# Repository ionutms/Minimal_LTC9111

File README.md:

# Minimal_LTC9111

## Overview

This repository contains a minimal KiCad design project for the Analog Devices LTC9111, an industrial Single-Pair Power over Ethernet (SPoE) Powered Device (PD) controller. The project is compliant with the IEEE 802.3cg standard and is designed for use in building and factory automation, security systems, and traffic control systems.

## Disclaimer

> [!NOTE]
> This project is provided "as is" and without any warranty, express or implied. For more details, please see the [LICENSE](LICENSE) file.

## About the LTC9111

The LTC9111 from Analog Devices is an industrial Single-Pair Power over Ethernet (SPoE) Powered Device (PD) controller. It is compliant with the IEEE 802.3cg standard and is designed for use in building and factory automation, security systems, and traffic control systems.

Key features include:

- **Wide Input Voltage Range:** The device operates with an input voltage from 2.3V to 60V.
- **Serial Communication Classification Protocol (SCCP):** This ensures that full operating voltage is only applied by the Power Sourcing Equipment (PSE) when a valid PD is connected.
- **Polarity Correction:** It drives low-side bridge MOSFETs for polarity correction.
- **Integrated Standby Regulator:** The LTC9111 includes an integrated 3.5V standby regulator.
- **Low Current Consumption:** It has a maximum current of 150µA during classification.
- **External MOSFET Drive:** It drives external N-channel MOSFETs for classification and to isolate output capacitance.
- **Package Options:** The LTC9111 is available in 12-pin MSOP and DFN 4mm × 3mm packages.
- **Temperature Range:** It has an operating junction temperature range of -40°C to +150°C.

## Project Structure

```
minimal_ltc9111/
├── minimal_ltc9111.kicad_sch       # Main schematic file
├── minimal_ltc9111.kicad_pcb       # PCB layout file
├── minimal_ltc9111.kicad_pro       # Project configuration file
├── fp-lib-table                     # Footprint library table
├── sym-lib-table                    # Symbol library table
├── project_jobs_set.kicad_jobset    # Project job settings
├── ibom.config.ini                  # Interactive BOM configuration
├── docs/                            # Documentation files
│   ├── pictures/                    # Images and photos
│   ├── schematics/                  # Schematic PDF exports
│   └── 3d_models/                   # 3D model files
└── KiCAD_Symbols_Generator/         # Submodule for symbol generation from CSV data
```

## Project Features

This design provides a minimal implementation of the LTC9111 with the following features:

- **Power Supply:**
  - VIN: +3.3V
- **Channel Configuration:**
  - Basic protection circuits for the Ethernet twisted pair.
- **Bill of Materials (BOM):**
  - Interactive HTML BOM (`ibom.html`) for easy component identification and sourcing.
- **Libraries:**
  - Comprehensive symbol and footprint libraries integrated as a submodule.
- **3D Model:**
  - Includes a 3D model of the board for better visualization.

## Getting Started

### Prerequisites

- [KiCad EDA](https://www.kicad.org/) version 9.0 or later installed on your system
- Git (for cloning the repository and submodule management)

### Opening the Project

1. **Clone the repository** (including submodules):
   ```bash
   git clone --recursive https://github.com/ionutms/Minimal_LTC9111.git
   ```
   
   If you've already cloned the repository without submodules, initialize them with:
   ```bash
   git submodule init
   git submodule update
   ```

2. **Open the project in KiCad**:
   - Launch KiCad
   - Click "Open Existing Project"
   - Navigate to the cloned repository folder
   - Select the `minimal_ltc9111.kicad_pro` file

3. **Explore the design**:
   - Open the schematic editor to view the circuit design
   - Open the PCB editor to view the board layout
   - Review the symbol and footprint libraries used in the design

### Project Files

- **Main schematic**: `minimal_ltc9111.kicad_sch` - Contains the primary circuit design with the LTC9111 and support components
- **PCB layout**: `minimal_ltc9111.kicad_pcb` - Physical board design file with proper component placement
- **Project configuration**: `minimal_ltc9111.kicad_pro` - KiCad project settings

## Dependencies

This project has the following dependencies:

### 1. KiCAD Symbols Generator

This repository uses [KiCAD_Symbols_Generator](https://github.com/ionutms/KiCAD_Symbols_Generator) as a submodule for custom symbol generation.

To initialize the submodule after cloning this repository:

```bash
git submodule update --init --recursive
```

### 2. 3D Models

This project requires the [3D_Models_Vault](https://github.com/ionutms/3D_Models_Vault) repository for 3D models.

#### Setup for KiCAD 9:

1. Clone the 3D models repository:
   ```bash
   git clone https://github.com/ionutms/3D_Models_Vault.git
   ```

2. In KiCAD 9, add an environment variable:
   - Variable name: `KICAD9_3D_MODELS_VAULT`
   - Variable value: Full path to where you cloned the 3D_Models_Vault repository

## Usage

After setting up the dependencies, open the project in KiCAD 9 to access all features including the 3D models.

## Symbol Generator Submodule

This project includes the KiCAD_Symbols_Generator as a submodule, which provides tools for generating KiCad symbols from CSV data files. For more information on using this tool, see the [KiCAD_Symbols_Generator documentation](minimal_ltc9111/KiCAD_Symbols_Generator/README.md).

## Documentation

The `docs` folder contains:
- Schematic PDF exports
- Images and photos of the design
- 3D model files (GLB and WRL formats)

## Visuals

The following images showcase the PCB design from different perspectives:

*Top View of the PCB*

*Side View of the PCB*

*Bottom View of the PCB*

## License

This project is licensed under the MIT License - see the [LICENSE](LICENSE) file for details.

## References

- [LTC9111 Datasheet](https://www.analog.com/media/en/technical-documentation/data-sheets/LTC9111.pdf)
- [KiCad EDA](https://www.kicad.org/)

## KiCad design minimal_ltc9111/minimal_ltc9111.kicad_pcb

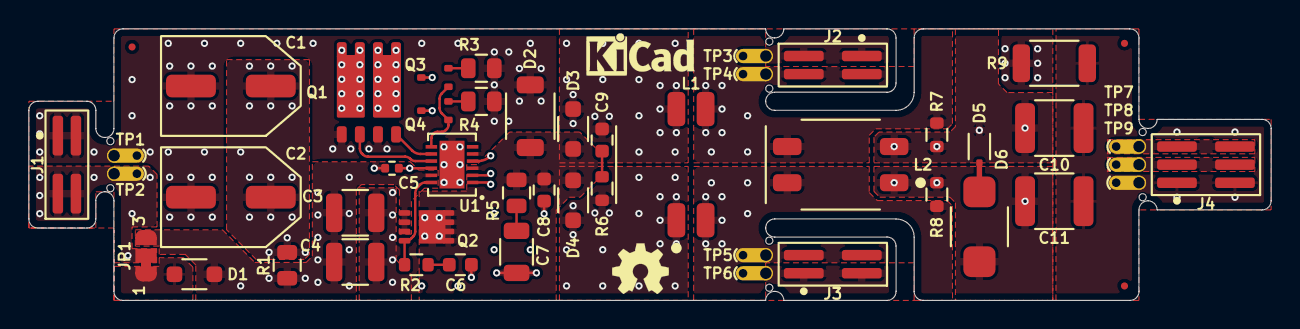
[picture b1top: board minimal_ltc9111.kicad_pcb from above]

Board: 4 copper layers, 87.1 x 19.0 mm, 54 parts (0 on the bottom side), 24 nets.

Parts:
C1, C2: 22 µF; C_023x0248_5_9x6_3Metric
C3, C4: 4.7 µF; C_1210_200_3225Metric
C5: 2.2 µF; C_0402_1005Metric
C6: 22 nF; C_0603_1608Metric
C7: 150 nF; C_1206_3216Metric
C8, C9: 47 nF; C_0603_1608Metric
C10, C11: 100 pF; C_1812_4532Metric
D1, D3, D4: 100.0 V; SOD123W
D2: 58 V; SOD128
D5: 3.3 V; SOD323
D6: 58 V; DO-214AA
FID1, FID2, FID3: Fiducial; Fiducial_0.5mm_Mask1mm
J1, J2, J3: FW-02-03-G-D-085-155
J4: FW-03-03-G-D-085-155
JP1: SolderJumper_3_Open; SolderJumper-3_P1.3mm_Bridged_1_2_RoundedPad1.0x1.5mm_Numbe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
L1: 68.0 µH; MSD1048
L2: 470 µH; SRF0905A
MB1, MB2, MB3: mouse-bite-midle-50mil-200mil
MB6: mouse-bite-50mil-200mil; mouse-bite-50mil-250mil
Q1: 100 V; LFPAK56D-8
Q2: 100.0 V; LFPAK33-8
Q3, Q4: 100 V; SOT-323
R1, R3, R4: 3.3 Ω; R_0805_2012Metric
R2, R6: 100 Ω; R_0603_1608Metric
R5: 40.2 Ω; R_0805_2012Metric
R7, R8: 10 kΩ; R_0603_1608Metric
R9: 4.7 MΩ; R_2010_5025Metric
TP1, TP2, TP3, TP4, TP5, TP6, TP7, TP8, TP9: TestPoint; TestPoint_THTPad_Castelated
U1: LTC9111RDE-PBF; 05-08-1695_ADI

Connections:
/BULK_OUT: C1.1, C2.1, R1.2
/CABLE+: C10.1, D5.1, J4.5, J4.6, L2.2, R7.1, TP7.1
/CABLE-: C11.1, D6.2, J4.3, J4.4, L2.1, R8.1, TP8.1
/IN: C8.1, D2.1, D3.1, D4.1, Q2.5 (D), R5.1, U1.3 (IN)
/LGATE1: Q1.2 (G1), U1.9 (LGATE1)
/LGATE2: Q1.4 (G2), U1.8 (LGATE2)
/OUT: C3.1, C4.1, D1.2, JP1.3 (B), Q2.1 (S), Q2.2 (S), Q2.3 (S), R1.1, U1.11 (OUT)
/OUT_SELECTED: J1.2, J1.4, JP1.2 (C), TP2.1
/POWER_IN_N: J3.3, J3.4, L1.2, L2.4, R8.2, TP5.1
/POWER_IN_P: J2.3, J2.4, L1.3, L2.3, R7.2, TP4.1
/POWER_N: C9.2, D3.2, L1.4, Q1.5 (D2), Q3.3 (D), U1.2 (SNS2)
/POWER_P: D4.2, L1.1, Q1.6 (D1), Q4.3 (D), R6.1, U1.1 (SNS1)
/SCCP: Q3.1 (G), Q4.1 (G), U1.7 (SCCP)
/STBY: C5.1, U1.4 (STBY), U1.10 (CLASSC)
Earth: C10.2, C11.2, J4.1, J4.2, R9.1, TP9.1
GND: C1.2, C2.2, C3.2, C4.2, C5.2, C6.2, C7.2, C8.2, D2.2, J1.1, J1.3, J2.1, J2.2, J3.1, J3.2, Q1.1 (S1), Q1.3 (S2), R3.2, R4.2, R9.2, TP1.1, TP3.1, TP6.1, U1.5 (CLASSV), U1.13 (GND)
unnamed: C6.1, R2.2
unnamed: C7.1, R5.2
unnamed: C9.1, R6.2
unnamed: D5.2, D6.1
unnamed: D1.1, JP1.1 (A)
unnamed: Q2.4 (G), R2.1, U1.12 (GATE)
unnamed: Q3.2 (S), R3.1
unnamed: Q4.2 (S), R4.1

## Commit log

2025-02-07 Add initial KiCad project files for minimal_ltc9111
2025-02-07 Add KiCad Symbol Generator submodule and library tables for minimal_ltc9111
2025-02-10 Add initial project files
2025-02-10 Backup
2025-02-10 Add glb 3D model
2025-02-24 Update UUIDs and add 3D viewer link in PCB and schematic files
2025-02-27 Update subproject commit in KiCAD_Symbol_Generator
2025-02-27 Update subproject commit and enhance component blacklist in ibom.config.ini; add new libraries in fp-lib-table and sym-lib-table
2025-02-27 Update minimal_ltc9111.glb binary file
2025-03-10 Update subproject commit in KiCAD_Symbol_Generator and modify minimal_ltc9111.glb binary file
2025-03-16 Remove submodule reference for KiCAD_Symbol_Generator
2025-03-16 Add submodule reference for KiCAD_Symbols_Generator
2025-03-16 Update footprint library URIs to reference KiCAD_Symbols_Generator
2025-03-18 Switch to KiCad 9
2025-03-19 Add .log files to .gitignore
2025-03-19 Add project job set configuration for minimal_ltc9111
2025-03-19 Update minimal_ltc9111 project files and add side image
2025-03-19 Refactor project job set configuration for minimal_ltc9111 to streamline 3D export settings
2025-03-19 Update minimal_ltc9111 binary files for improved asset quality
2025-03-20 Add special execute command for rendering top view in project job set
2025-03-20 Update subproject commit for KiCAD Symbols Generator
2025-03-20 Add top and side images for minimal_ltc9111 and update project configuration
2025-03-21 Update project job set for minimal_ltc9111 to enhance rendering commands and output paths
2025-03-21 Remove outdated top and side images for minimal_ltc9111 and add new 3D model and front, right images
2025-03-21 small updates
2025-03-21 Update 3D model and images for minimal_ltc9111
2025-03-22 Update README.md to include project dependencies and setup instructions
2025-03-31 Add error check for text on edge cuts in minimal_ltc9111 project
2025-03-31 Update 3D models and images for minimal_ltc9111
2025-04-14 development backup
2025-04-14 Adjust render command parameters for minimal_ltc9111 side image
2025-04-18 Update KiCad documentation (schematics and PCB renders)
2025-04-18 Add KiCad configuration file and update workflow to use custom zoom factor
2025-04-23 Refactor KiCad configuration handling and update workflow to utilize new zoom factors and parameters
2025-04-23 Update KiCad documentation for minimal_ltc9111 (schematics and PCB renders)
2025-04-24 Enhance KiCad job workflow: improve configuration extraction and 3D model handling
2025-04-24 Update KiCad configuration: adjust zoom factors and pan settings
2025-04-24 Remove obsolete schematics and images for minimal_ltc9111
2025-05-24 Add GitHub Actions workflow to generate KiCad 3D models
2025-05-25 Update GitHub Actions workflow for generating KiCad 3D models
2025-08-18 Add bottom view rendering support with configurable zoom factor
2025-08-22 Update GitHub workflow files for KiCAD jobs and 3D models generation
2025-08-29 Update KiCad Docker image version and improve workflow outputs
2025-09-02 Update README.md with comprehensive project documentation
2025-10-05 chore: update workflows from central repository
2025-10-05 chore: update workflows and kicad config from central repository
2025-10-26 Update kicad-config workflow settings
